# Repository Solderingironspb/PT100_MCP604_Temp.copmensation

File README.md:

# Плата преобразователя температуры с датчика PT100 (3-проводное подключение) с температурной компенсацией.

### Ссылки:
  **[YouTube](https://www.youtube.com/channel/UCzZKTNVpcMSALU57G1THoVw)**
  
  **[GitHub](https://github.com/Solderingironspb)**  
  
  **[ВКонтакте](https://vk.com/solderingiron.stm32)** 
  
  **[Статья на ЯндексДзен](https://dzen.ru/a/Y9DrUOmsOTVF6Tv8)**

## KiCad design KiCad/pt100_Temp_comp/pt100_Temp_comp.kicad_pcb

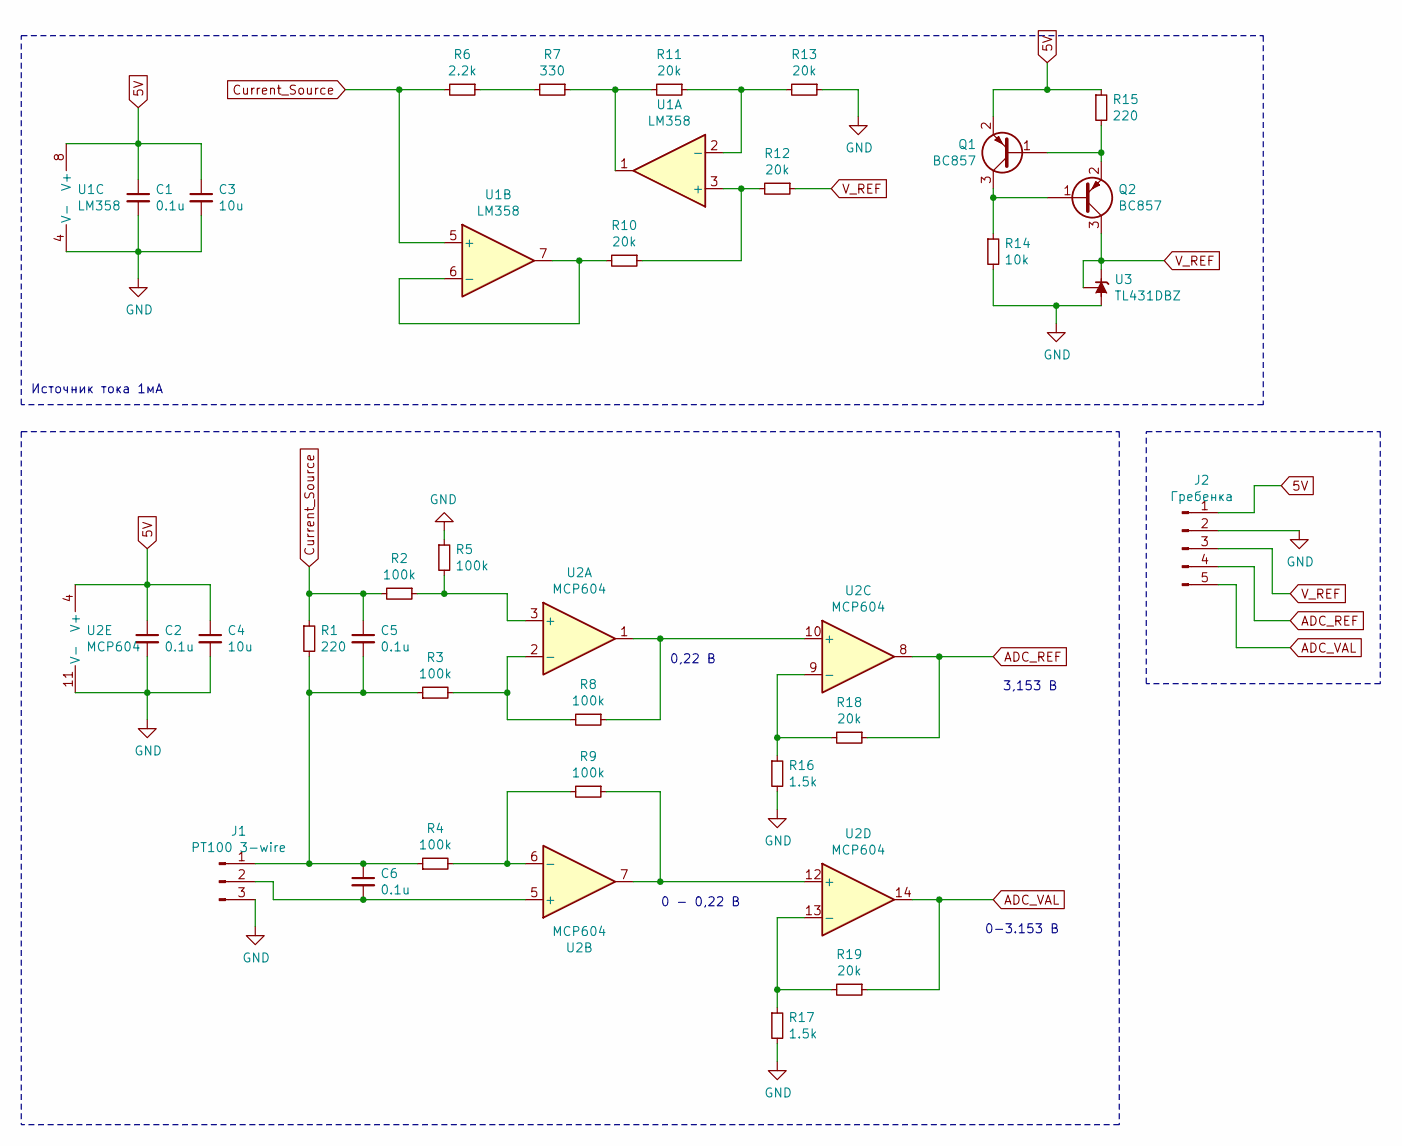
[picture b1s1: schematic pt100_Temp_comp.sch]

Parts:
C1, C2, C5, C6: 0.1u; C_0805_2012Metric
C3, C4: 10u; C_0805_2012Metric
J1: PT100 3-wire; TerminalBlock_Altech_AK300-3_P5.00mm
J2: Гребенка; PinSocket_1x05_P2.54mm_Vertical
Q1, Q2: BC857; SOT-23
R1, R15: 220; R_0805_2012Metric
R2, R3, R4, R5, R8, R9: 100k; R_0805_2012Metric
R6: 2.2k; R_0805_2012Metric
R7: 330; R_0805_2012Metric
R10, R11, R12, R13, R18, R19: 20k; R_0805_2012Metric
R14: 10k; R_0805_2012Metric
R16, R17: 1.5k; R_0805_2012Metric
U1: LM358; SO-8_5.3x6.2mm_P1.27mm
U2: MCP604; SOIC-14_3.9x8.7mm_P1.27mm
U3: TL431DBZ; SOT-23

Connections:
5V: C1.1, C2.1, C3.1, C4.1, J2.1, Q1.2 (E), R15.1, U1.8 (V+), U2.4 (V+)
ADC_REF: J2.4, R18.1, U2.8
ADC_VAL: J2.5, R19.1, U2.14
Current_Source: C5.1, R1.1, R2.2, R6.2, U1.5 (+)
GND: C1.2, C2.2, C3.2, C4.2, J1.3, J2.2, R5.1, R13.1, R14.2, R16.2, R17.2, U1.4 (V-), U2.11 (V-), U3.3 (A)
unnamed: C5.2, C6.1, J1.1, R1.2, R3.1, R4.1
unnamed: C6.2, J1.2, U2.5 (+)
unnamed: Q1.1 (B), Q2.2 (E), R15.2
unnamed: Q1.3 (C), Q2.1 (B), R14.1
unnamed: R2.1, R5.2, U2.3 (+)
unnamed: R3.2, R8.2, U2.2 (-)
unnamed: R4.2, R9.2, U2.6 (-)
unnamed: R6.1, R7.2
unnamed: R8.1, U2.1, U2.10 (+)
unnamed: R9.1, U2.7, U2.12 (+)
unnamed: R10.1, R12.2, U1.3 (+)
unnamed: R10.2, U1.6 (-), U1.7
unnamed: R11.1, R13.2, U1.2 (-)
unnamed: R7.1, R11.2, U1.1
unnamed: R16.1, R18.2, U2.9 (-)
unnamed: R17.1, R19.2, U2.13 (-)
V_REF: J2.3, Q2.3 (C), R12.1, U3.1 (K), U3.2 (REF)

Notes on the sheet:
Источник тока 1мА
0,22 В
0 - 0,22 В
3,153 В
0-3.153 В

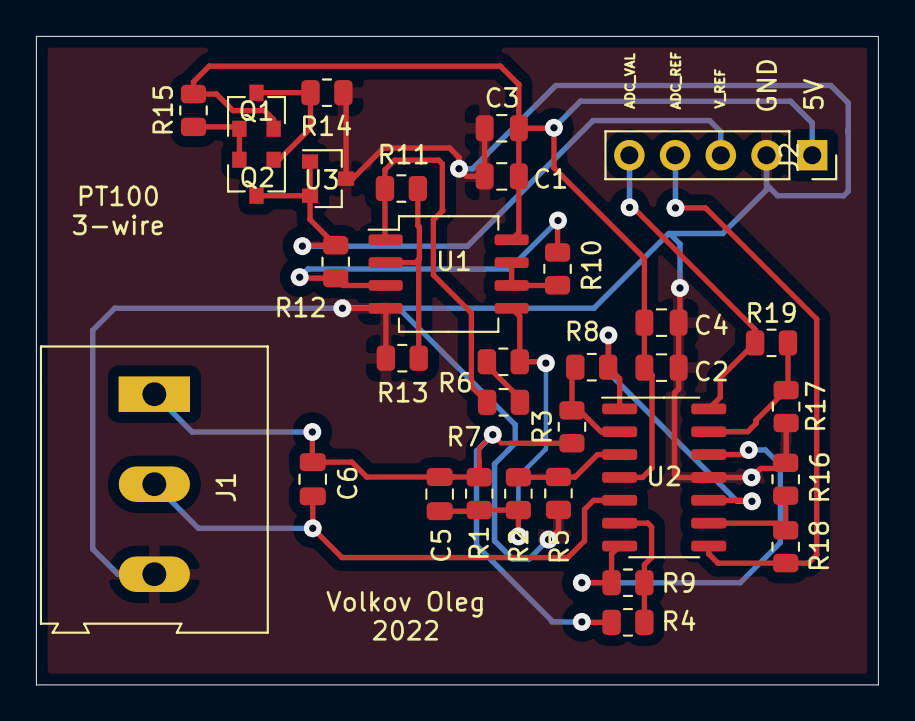
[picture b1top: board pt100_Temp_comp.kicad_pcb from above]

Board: 2 copper layers, 46.8 x 36.0 mm, 32 parts (0 on the bottom side), 22 nets.

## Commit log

2023-01-25 add info
